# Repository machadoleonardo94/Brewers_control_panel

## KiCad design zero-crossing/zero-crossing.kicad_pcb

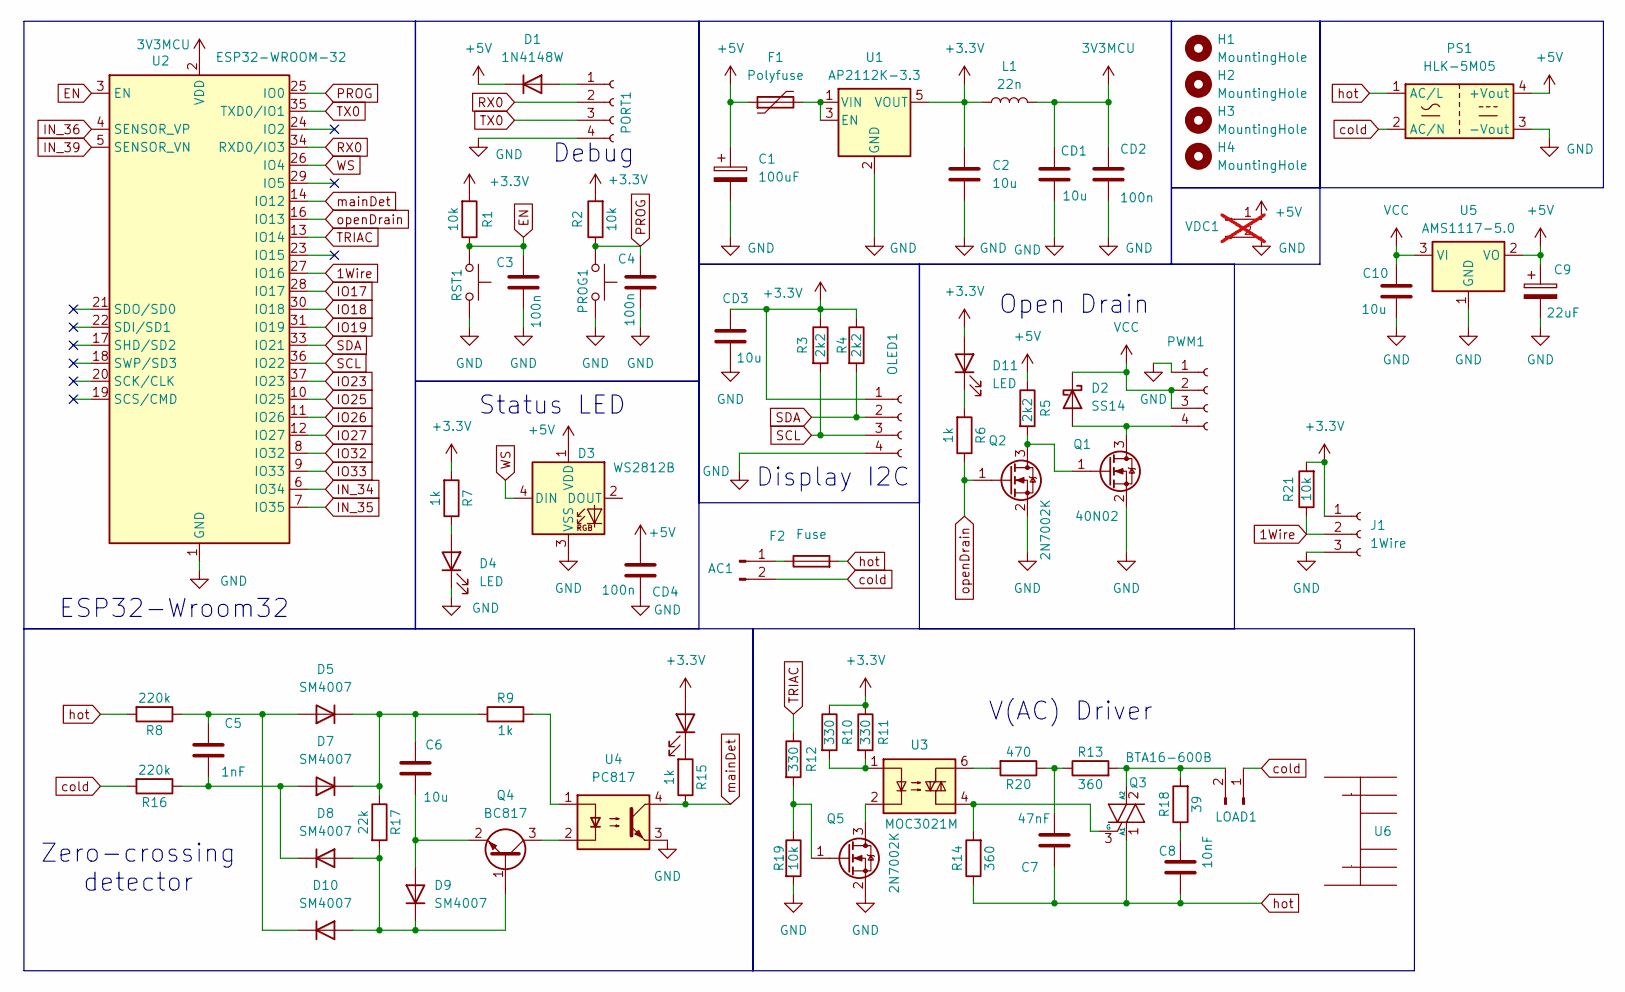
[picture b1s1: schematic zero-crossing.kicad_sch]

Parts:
AC1: Conn_01x02_Pin; PhoenixContact_GMSTBA_2,5_2-G-7,62_1x02_P7.62mm_Horizontal
C1: 100uF; C_Elec_6.3x7.7; LCSC C99837
C2, C6, C10: 10u; C_0805_2012Metric; LCSC C77075
C3, C4: 100n; C_0805_2012Metric; LCSC C2909631
C5: 1nF; C_0805_2012Metric; Part Number C0805C104J5RALTU; LCSC C2909631
C7: 47nF; C_Rect_L11.0mm_W4.3mm_P10.00mm_MKT; Part Number C0805C104J5RALTU; LCSC C2909631
C8: 10nF; C_Rect_L7.0mm_W3.5mm_P5.00mm; Part Number C0805C104J5RALTU; LCSC C2909631
C9: 22uF; CP_EIA-3216-18_Kemet-A_Pad1.58x1.35mm_HandSolder
CD1, CD3: 10u; C_0805_2012Metric; LCSC C77075
CD2, CD4: 100n; C_0805_2012Metric; LCSC C2909631
D1: 1N4148W; D_SOD-123; LCSC C82544
D2: SS14; D_SMA; LCSC C2909920
D3: WS2812B; LED_WS2812B_PLCC4_5.0x5.0mm_P3.2mm; LCSC 1
D4, D6, D11: LED; LED_0805_2012Metric_Pad1.15x1.40mm_HandSolder; LCSC C84256
D5, D7, D8, D9, D10: SM4007; D_MELF
F1: Polyfuse; Fuse_1206_3216Metric_Pad1.42x1.75mm_HandSolder; LCSC C22446878
F2: Fuse; Fuseholder_Clip-5x20mm_Bel_FC-203-22_Lateral_P17.80x5.00mm_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
H1, H2, H3, H4: MountingHole; MountingHole_3.2mm_M3
J1: 1Wire; TerminalBlock_Xinya_XY308-2.54-3P_1x03_P2.54mm_Horizontal
L1: 22n; L_0805_2012Metric; LCSC 1
LOAD1: Conn_01x02_Pin; PhoenixContact_GMSTBA_2,5_2-G-7,62_1x02_P7.62mm_Horizontal
OLED1: Conn_01x04_Socket; Hirose_DF13C_CL535-0404-8-51_1x04-1MP_P1.25mm_Vertical; LCSC 1
PORT1: Conn_01x04_Socket; Hirose_DF13C_CL535-0404-8-51_1x04-1MP_P1.25mm_Vertical; LCSC 1
PROG1: SW_Push; SW_SPST_PTS647_Sx38; LCSC C455246
PS1: HLK-5M05; Converter_ACDC_Hi-Link_HLK-5Mxx
PWM1: Conn_01x03_Socket; TerminalBlock_Phoenix_MKDS-1,5-4_1x04_P5.00mm_Horizontal
Q1: 40N02; TO-252-2
Q2, Q5: 2N7002K; SOT-23; LCSC C65189
Q3: BTA16-600B; TO-220-3_Vertical; LCSC C7471857
Q4: BC817; SOT-23
R1, R2, R19, R21: 10k; R_0805_2012Metric; LCSC C17414
R3, R4, R5: 2k2; R_0805_2012Metric; LCSC C17520
R6, R7, R9, R15: 1k; R_0805_2012Metric; LCSC C95781
R8, R16: 220k; R_0805_2012Metric; LCSC C95781
R10, R11, R12: 330; R_0805_2012Metric; LCSC C17630
R13, R14: 360; R_Axial_DIN0411_L9.9mm_D3.6mm_P15.24mm_Horizontal; LCSC C95781
R17: 22k; R_0805_2012Metric; LCSC C95781
R18: 39; R_Axial_DIN0411_L9.9mm_D3.6mm_P15.24mm_Horizontal; LCSC C95781
R20: 470; R_Axial_DIN0411_L9.9mm_D3.6mm_P15.24mm_Horizontal; LCSC C95781
RST1: SW_Push; SW_SPST_PTS647_Sx38; LCSC C455246
U1: AP2112K-3.3; SOT-23-5; LCSC C51118
U2: ESP32-WROOM-32; ESP32-WROOM-32U; LCSC C2980301
U3: MOC3021M; SMDIP-6_W9.53mm; LCSC C115465
U4: PC817; SMDIP-4_W7.62mm; LCSC C5451664
U5: AMS1117-5.0; SOT-223-3_TabPin2
U6: HEATSINK-TH_L34.0-W12.0; Manufacturer Part 34X12-25; LCSC Part Name 文豪永顺 34X12-25
VDC1: Conn_01x02_Pin; TerminalBlock_Phoenix_MKDS-1,5-2-5.08_1x02_P5.08mm_Horizont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; not fitted

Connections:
1Wire: J1.2, R21.1, U2.27 (IO16)
3V3MCU: CD1.1, CD2.1, L1.2, U2.2 (VDD)
+3.3V: C2.1, CD3.1, D6.2 (A), D11.2 (A), J1.1, L1.1, OLED1.1, R1.2, R2.2, R3.1, R4.1, R7.2, R10.1, R11.1, R21.2, U1.5 (VOUT)
+5V: C1.1, C9.1, CD4.1, D1.1 (K), D3.1 (VDD), F1.1, PS1.4 (+Vout), R5.1, U5.2 (VO), VDC1.1
EN: C3.1, R1.1, RST1.2, U2.3 (EN)
GND: C1.2, C2.2, C3.2, C4.2, C9.2, C10.2, CD1.2, CD2.2, CD3.2, CD4.2, D3.3 (VSS), D4.1 (K), J1.3, OLED1.4, PORT1.4, PROG1.1, PS1.3 (-Vout), PWM1.1, Q1.2 (S), Q2.2 (S), Q5.2 (S), R19.2, RST1.1, U1.2 (GND), U2.1 (GND), U2.15 (GND), U2.38 (GND), U2.39 (GND), U4.3, U5.1 (GND), VDC1.2
IN_34: U2.6 (IO34)
IN_35: U2.7 (IO35)
IN_36: U2.4 (SENSOR_VP)
IN_39: U2.5 (SENSOR_VN)
IO17: U2.28 (IO17)
IO18: U2.30 (IO18)
IO19: U2.31 (IO19)
IO23: U2.37 (IO23)
IO25: U2.10 (IO25)
IO26: U2.11 (IO26)
IO27: U2.12 (IO27)
IO32: U2.8 (IO32)
IO33: U2.9 (IO33)
unnamed: AC1.1, F2.1
unnamed: C7.1, R13.1, R20.1
unnamed: C8.2, R18.1
unnamed: D1.2 (A), PORT1.1
unnamed: D2.2 (A), PWM1.4, Q1.3 (D)
unnamed: D4.2 (A), R7.1
unnamed: C6.1, D5.1 (K), D7.1 (K), R9.1, R17.1
unnamed: D6.1 (K), R15.2
unnamed: C5.1, D7.2 (A), D8.1 (K), R16.1
unnamed: C6.2, D9.2 (A), Q4.2 (E)
unnamed: D8.2 (A), D9.1 (K), D10.2 (A), Q4.1 (B), R17.2
unnamed: C5.2, D5.2 (A), D10.1 (K), R8.1
unnamed: D11.1 (K), R6.2
unnamed: LOAD1.2, Q3.2 (A2), R13.2, R18.2
unnamed: Q1.1 (G), Q2.3 (D), R5.2
unnamed: Q3.3 (G), R14.2, U3.4
unnamed: Q4.3 (C), U4.2
unnamed: Q5.3 (D), U3.2
unnamed: Q5.1 (G), R12.2, R19.1
unnamed: R9.2, U4.1
unnamed: R10.2, R11.2, U3.1
unnamed: R20.2, U3.6
unnamed: F1.2, U1.1 (VIN), U1.3 (EN)
PROG: C4.1, PROG1.2, R2.1, U2.25 (IO0)
RX0: PORT1.2, U2.34 (RXD0/IO3)
SCL: OLED1.3, R3.2, U2.36 (IO22)
SDA: OLED1.2, R4.2, U2.33 (IO21)
TRIAC: R12.1, U2.13 (IO14)
TX0: PORT1.3, U2.35 (TXD0/IO1)
VCC: C10.1, D2.1 (K), PWM1.2, PWM1.3, U5.3 (VI)
WS: D3.4 (DIN), U2.26 (IO4)
cold: AC1.2, LOAD1.1, PS1.2 (AC/N), R16.2
hot: C7.2, C8.1, F2.2, PS1.1 (AC/L), Q3.1 (A1), R8.2, R14.1
mainDet: R15.1, U2.14 (IO12), U4.4
openDrain: Q2.1 (G), R6.1, U2.16 (IO13)

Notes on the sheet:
Zero-crossing detector
Status LED
Display I2C
V(AC) Driver
Debug
ESP32-Wroom32
Open Drain

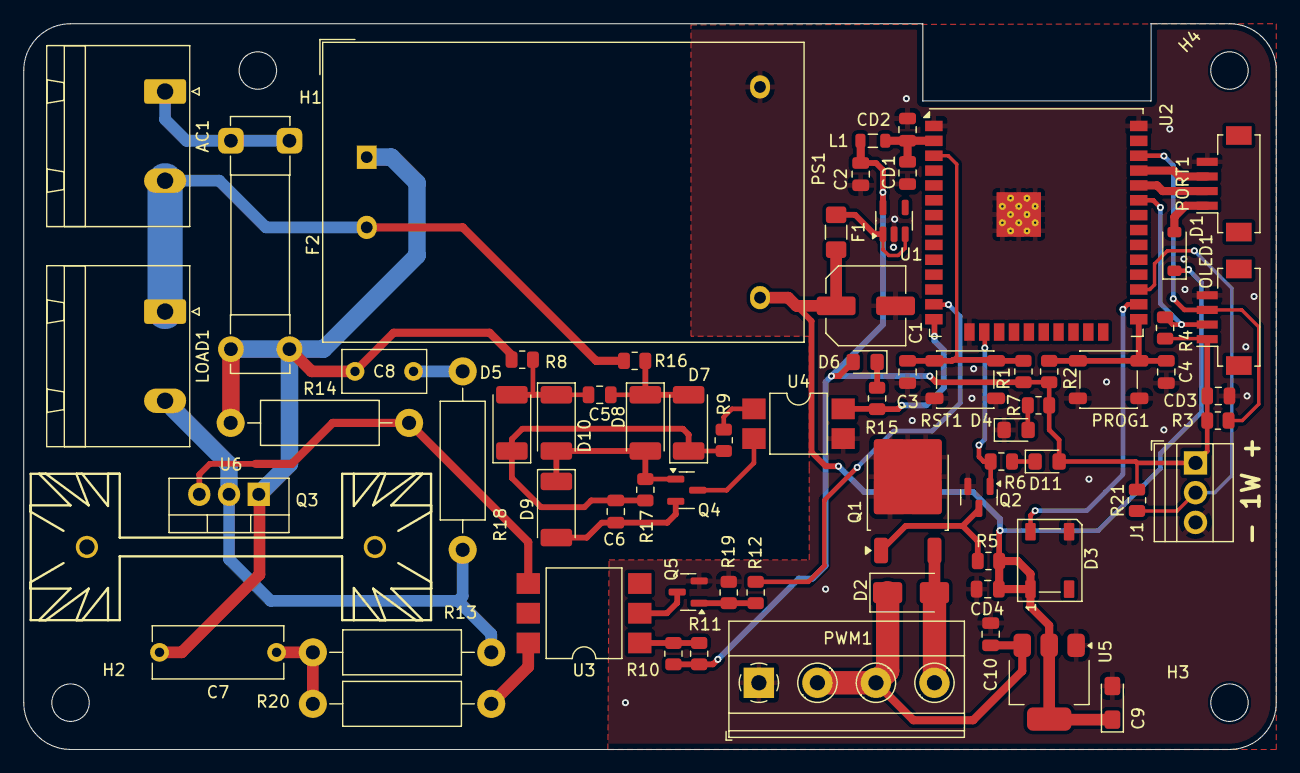
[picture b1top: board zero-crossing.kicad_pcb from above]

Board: 2 copper layers, 107.0 x 62.0 mm, 73 parts (0 on the bottom side), 41 nets.

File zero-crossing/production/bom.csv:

Designator,Footprint,Quantity,Value,LCSC Part #
"AC1, LOAD1","PhoenixContact_GMSTBA_2,5_2-G-7,62_1x02_P7.62mm_Horizontal",2,Conn_01x02_Pin,
C1,C_Elec_6.3x7.7,1,100uF,C99837
"C10, C2, C6, CD1, CD3",0805,5,10u,C77075
"C3, C4, CD2, CD4",0805,4,100n,C2909631
C5,0805,1,1nF,C2909631
C7,C_Rect_L11.0mm_W4.3mm_P10.00mm_MKT,1,47nF,C2909631
C8,C_Rect_L7.0mm_W3.5mm_P5.00mm,1,10nF,C2909631
C9,CP_EIA-3216-18_Kemet-A_Pad1.58x1.35mm_HandSolder,1,22uF,
D1,D_SOD-123,1,1N4148W,C82544
"D10, D5, D7, D8, D9",D_MELF,5,SM4007,
"D11, D4, D6",0805,3,LED,C84256
D2,D_SMA,1,SS14,C2909920
D3,LED_WS2812B_PLCC4_5.0x5.0mm_P3.2mm,1,WS2812B,1
F1,1206,1,Polyfuse,C22446878
F2,Fuseholder_Clip-5x20mm_Bel_FC-203-22_Lateral_P17.80x5.00mm_D1.17mm_Horizontal,1,Fuse,
J1,TerminalBlock_Xinya_XY308-2.54-3P_1x03_P2.54mm_Horizontal,1,1Wire,
L1,0805,1,22n,1
"OLED1, PORT1",Hirose_DF13C_CL535-0404-8-51_1x04-1MP_P1.25mm_Vertical,2,Conn_01x04_Socket,1
"PROG1, RST1",SW_SPST_PTS647_Sx38,2,SW_Push,C455246
PS1,Converter_ACDC_Hi-Link_HLK-5Mxx,1,HLK-5M05,
PWM1,"TerminalBlock_Phoenix_MKDS-1,5-4_1x04_P5.00mm_Horizontal",1,Conn_01x03_Socket,
Q1,TO-252-2,1,40N02,
"Q2, Q5",SOT-23,2,2N7002K,C65189
Q3,TO-220-3_Vertical,1,BTA16-600B,C7471857
Q4,SOT-23,1,BC817,
"R1, R19, R2, R21",0805,4,10k,C17414
"R10, R11, R12",0805,3,330,C17630
"R13, R14",R_Axial_DIN0411_L9.9mm_D3.6mm_P15.24mm_Horizontal,2,360,C95781
"R15, R6, R7, R9",0805,4,1k,C95781
"R16, R8",0805,2,220k,C95781
R17,0805,1,22k,C95781
R18,R_Axial_DIN0411_L9.9mm_D3.6mm_P15.24mm_Horizontal,1,39,C95781
R20,R_Axial_DIN0411_L9.9mm_D3.6mm_P15.24mm_Horizontal,1,470,C95781
"R3, R4, R5",0805,3,2k2,C17520
U1,SOT-23-5,1,AP2112K-3.3,C51118
U2,ESP32-WROOM-32U,1,ESP32-WROOM-32,C2980301
U3,SMDIP-6_W9.53mm,1,MOC3021M,C115465
U4,SMDIP-4_W7.62mm,1,PC817,C5451664
U5,SOT-223-3_TabPin2,1,AMS1117-5.0,
U6,HEATSINK-TH_L34.0-W12.0,1,~,

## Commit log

2026-02-01 Initial release
2026-02-01 Base firmware
2026-02-01 Added PDF schematics
2026-02-17 ESPHome
    Initial firmware for ESPHome.
    Includes PID controller, manual and auto tuning of parameters
